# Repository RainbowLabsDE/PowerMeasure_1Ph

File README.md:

# PowerMeasure_1Ph

this repo is still undergoing major changes and should not yet be rebuilt

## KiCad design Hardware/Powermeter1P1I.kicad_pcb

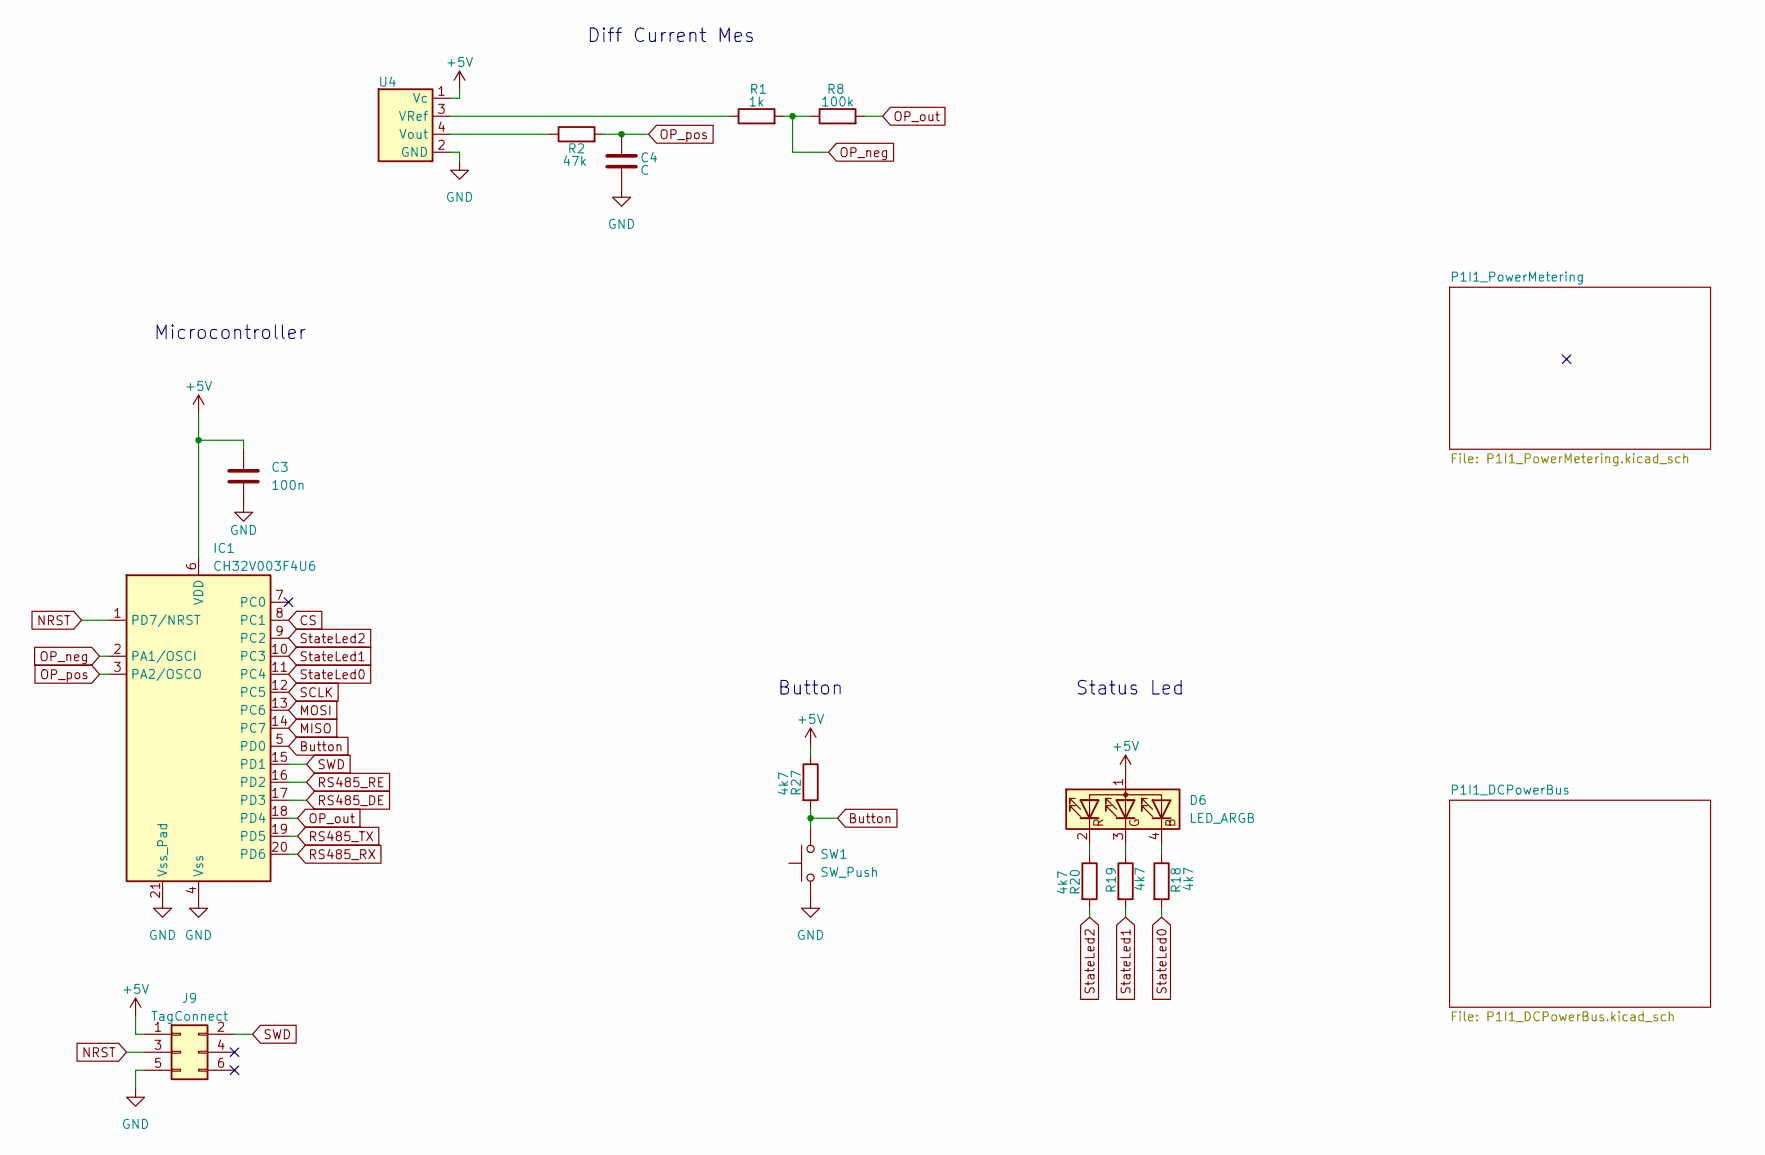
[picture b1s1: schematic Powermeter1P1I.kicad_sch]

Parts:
C3: 100n; C_0402_1005Metric
C4: C; C_0402_1005Metric
D6: LED_ARGB; LED-ARRAY-SMD_MHS110FRGBCT
IC1: CH32V003F4U6; QFN-20-1EP_3x3mm_P0.4mm_EP1.65x1.65mm_ThermalVias
J9: TagConnect; Tag-Connect_TC2030-IDC-NL_2x03_P1.27mm_Vertical
R1: 1k; R_0402_1005Metric
R2: 47k; R_0402_1005Metric
R8: 100k; R_0402_1005Metric
R18, R19, R20, R27: 4k7; R_0402_1005Metric
SW1: SW_Push; SW-SMD_TS24CA
U4: VACDiff

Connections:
+5V: C3.1, D6.1 (A), IC1.6 (VDD), J9.1, R27.1, U4.1 (Vc); also elsewhere on the board
Button: IC1.5 (PD0), R27.2, SW1.2
CS: IC1.8 (PC1); also elsewhere on the board
GND: C3.2, C4.2, IC1.4 (Vss), IC1.21 (Vss_Pad), J9.5, SW1.1, U4.2 (GND); also elsewhere on the board
MISO: IC1.14 (PC7); also elsewhere on the board
MOSI: IC1.13 (PC6); also elsewhere on the board
NRST: IC1.1 (PD7/NRST), J9.3
unnamed: D6.4 (BK), R18.1
unnamed: D6.3 (GK), R19.1
unnamed: D6.2 (RK), R20.1
unnamed: R1.1, U4.3 (VRef)
unnamed: R2.1, U4.4 (Vout)
OP_neg: IC1.2 (PA1/OSCI), R1.2, R8.1
OP_out: IC1.18 (PD4), R8.2
OP_pos: C4.1, IC1.3 (PA2/OSCO), R2.2
RS485_DE: IC1.17 (PD3); also elsewhere on the board
RS485_RE: IC1.16 (PD2); also elsewhere on the board
RS485_RX: IC1.20 (PD6); also elsewhere on the board
RS485_TX: IC1.19 (PD5); also elsewhere on the board
SCLK: IC1.12 (PC5); also elsewhere on the board
SWD: IC1.15 (PD1), J9.2
StateLed0: IC1.11 (PC4), R18.2
StateLed1: IC1.10 (PC3), R19.2
StateLed2: IC1.9 (PC2), R20.2

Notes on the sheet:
Status Led
Microcontroller
Button
Diff Current Mes

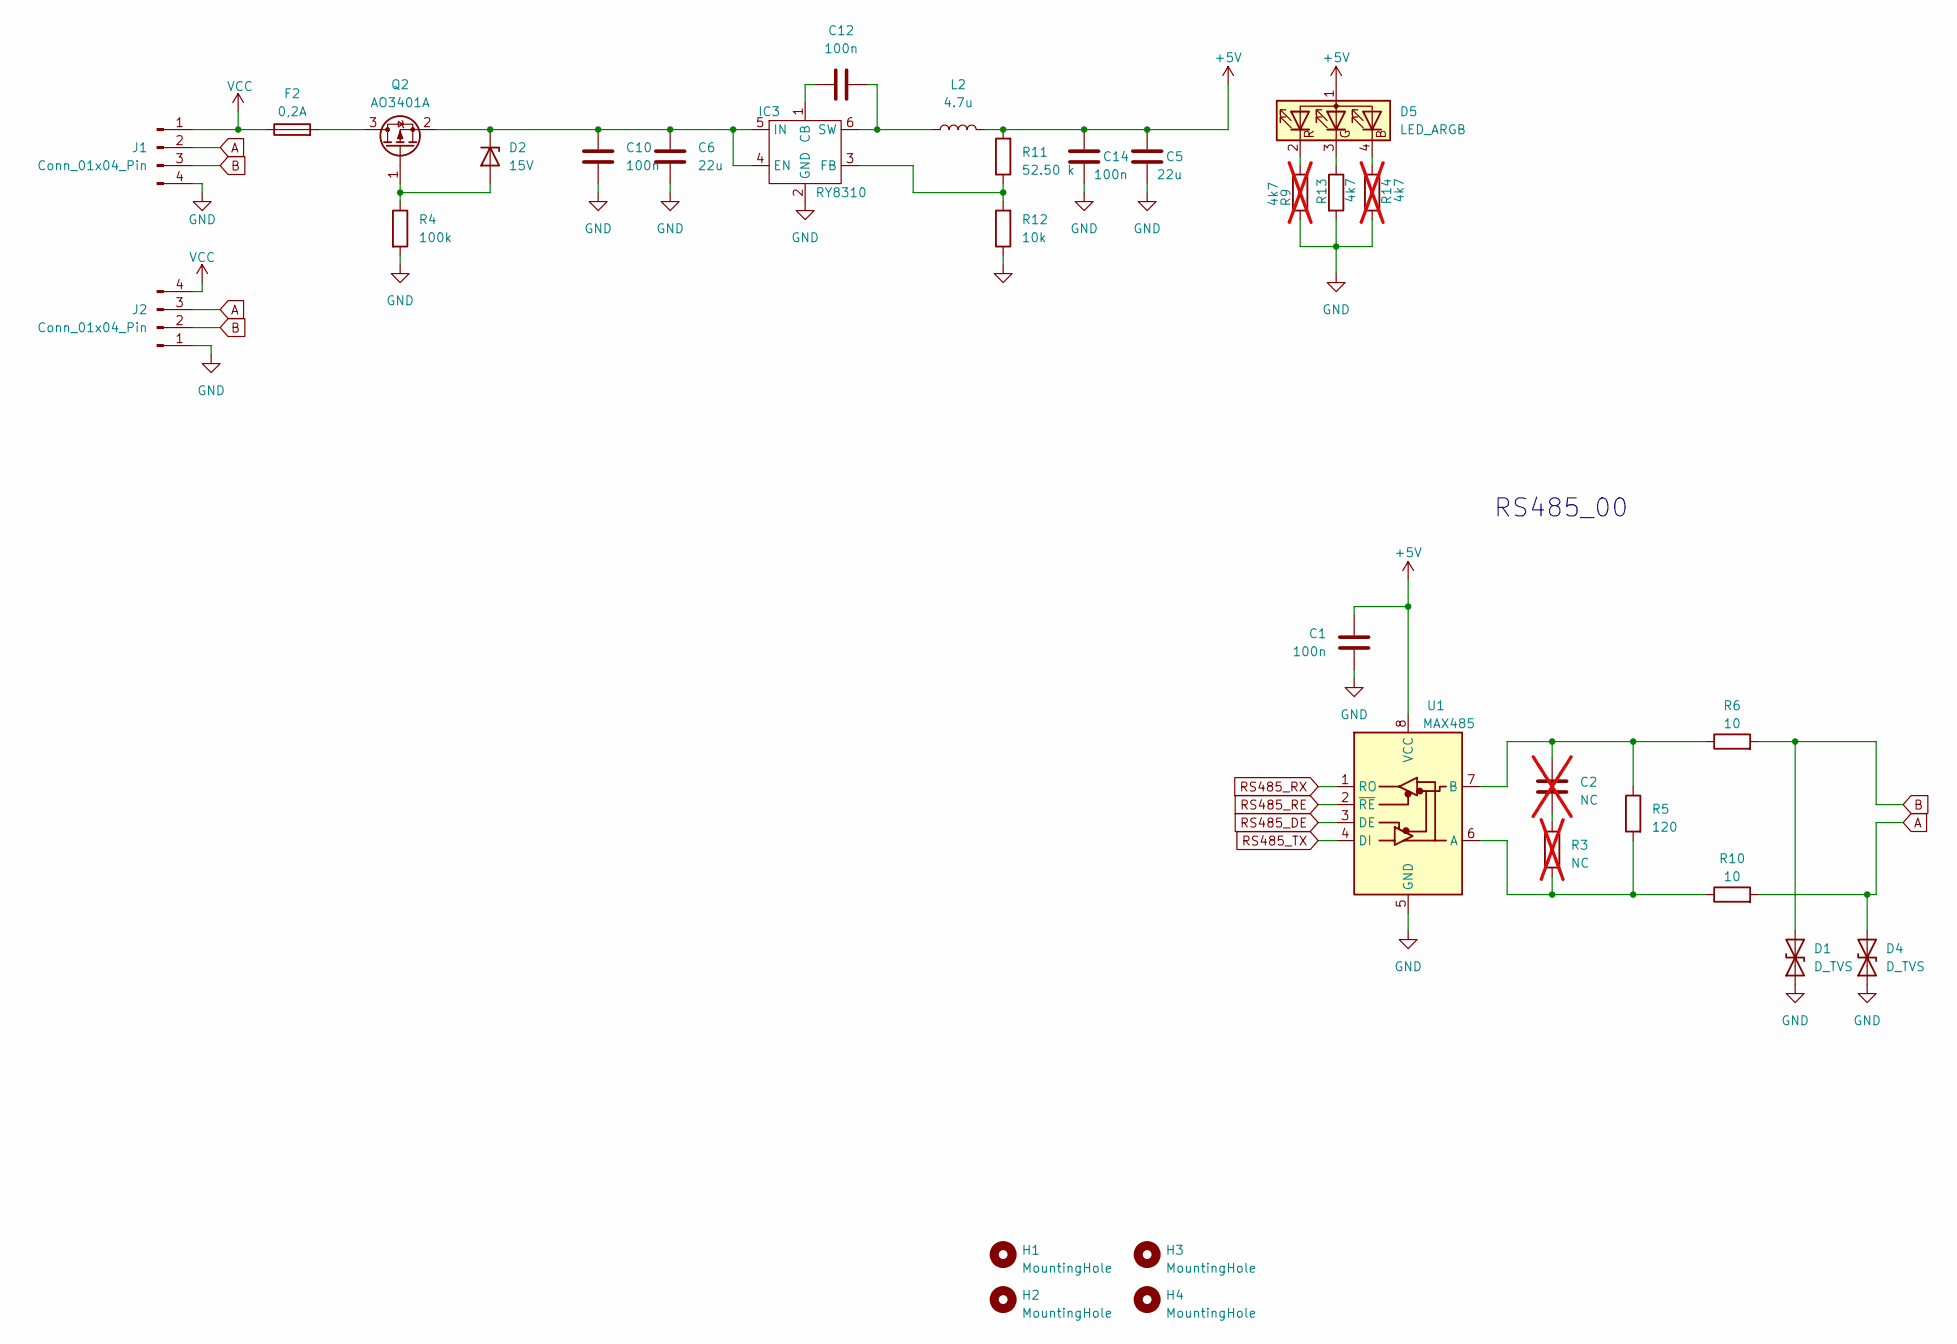
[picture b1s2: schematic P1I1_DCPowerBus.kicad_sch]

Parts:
C1, C10, C12, C14: 100n; C_0402_1005Metric
C2: NC; C_0402_1005Metric; not fitted
C5, C6: 22u; C_1210_3225Metric
D1, D4: D_TVS; D_0402_1005Metric
D2: 15V; D_SOD-323
D5: LED_ARGB; LED-ARRAY-SMD_MHS110FRGBCT
F2: 0,2A; Fuse_0603_1608Metric
H1, H2, H3, H4: MountingHole; MountingHole_4.3mm_M4
IC3: RY8310; SOT-23-6
J1, J2: Conn_01x04_Pin; CONN-SMD_HCZZ0451-4
L2: 4.7u; IND-SMD_L2.0-W1.6
Q2: AO3401A; TSOT-23
R3: NC; R_0402_1005Metric; not fitted
R4: 100k; R_0402_1005Metric
R5: 120; C_0402_1005Metric
R6, R10: 10; R_1206_3216Metric
R9, R14: 4k7; R_0402_1005Metric; not fitted
R11: 52.50 k; R_0402_1005Metric
R12: 10k; R_0402_1005Metric
R13: 4k7; R_0402_1005Metric
U1: MAX485; SOIC-8_3.9x4.9mm_P1.27mm

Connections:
+5V: C1.1, C5.1, C14.1, D5.1 (A), L2.2, R11.2, U1.8 (VCC); also elsewhere on the board
A: D4.2 (A2), J1.2, J2.3, R10.2
B: D1.2 (A2), J1.3, J2.2, R6.2
GND: C1.2, C5.2, C6.2, C10.2, C14.2, D1.1 (A1), D4.1 (A1), IC3.2 (GND), J1.4, J2.1, R4.2, R9.2, R12.1, R13.2, R14.2, U1.5 (GND); also elsewhere on the board
unnamed: C2.2, R3.2
unnamed: D2.2 (A), Q2.1 (G), R4.1
unnamed: C6.1, C10.1, D2.1 (K), IC3.4 (EN), IC3.5 (IN), Q2.2 (S)
unnamed: D5.4 (BK), R14.1
unnamed: D5.3 (GK), R13.1
unnamed: D5.2 (RK), R9.1
unnamed: C12.1, IC3.1 (CB)
unnamed: IC3.3 (FB), R11.1, R12.2
unnamed: C12.2, IC3.6 (SW), L2.1
unnamed: F2.2, Q2.3 (D)
unnamed: R3.1, R5.2, R10.1, U1.6 (A)
unnamed: C2.1, R5.1, R6.1, U1.7 (B)
RS485_DE: U1.3 (DE); also elsewhere on the board
RS485_RE: U1.2 (~RE); also elsewhere on the board
RS485_RX: U1.1 (RO); also elsewhere on the board
RS485_TX: U1.4 (DI); also elsewhere on the board
VCC: F2.1, J1.1, J2.4

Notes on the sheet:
RS485_00

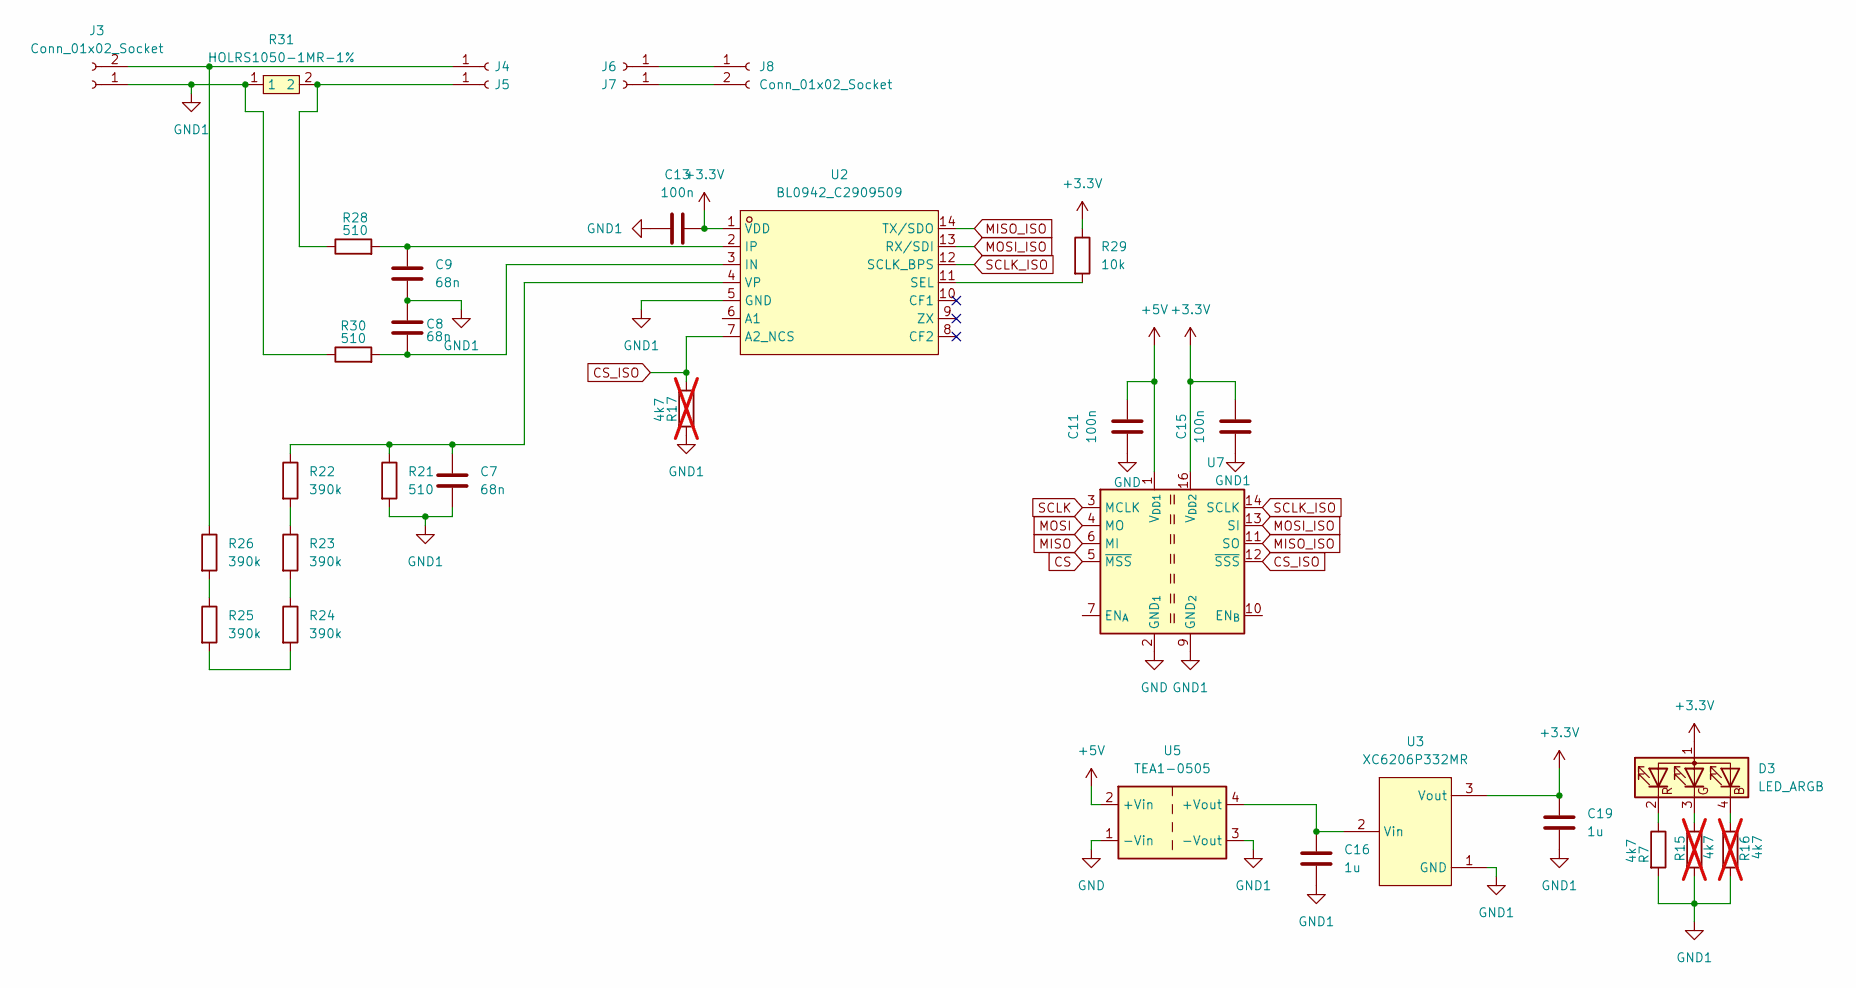
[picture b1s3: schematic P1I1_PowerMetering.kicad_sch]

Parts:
C7, C8, C9: 68n; C_0402_1005Metric
C11, C13, C15: 100n; C_0402_1005Metric
C16, C19: 1u; C_0402_1005Metric
D3: LED_ARGB; LED-ARRAY-SMD_MHS110FRGBCT
J3, J8: Conn_01x02_Socket; LPT2,5-2-5,0
J4, J5, J6, J7: Conn_01x01_Socket; TestPoint_THTPad_3.0x3.0mm_Drill1.5mm
R7: 4k7; R_0402_1005Metric
R15, R16, R17: 4k7; R_0402_1005Metric; not fitted
R21, R28, R30: 510; R_0603_1608Metric
R22, R23, R24, R25, R26: 390k; R_0603_1608Metric
R29: 10k; R_0402_1005Metric
R31: HOLRS1050-1MR-1%; R3920; LCSC Part C481472
U2: BL0942_C2909509; TSSOP-14_L5.0-W4.4-P0.65-LS6.4-BL; LCSC Part C2909509
U3: XC6206P332MR; SOT-23-3_L2.9-W1.6-P1.90-LS2.8-BR; LCSC Part C5446
U5: TEA1-0505; Converter_DCDC_TRACO_TEA1-xxxx_THT
U7: SOIC-16W_7.5x10.3mm_P1.27mm

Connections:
+3.3V: C13.2, C15.2, C19.1, D3.1 (A), R29.1, U2.1 (VDD), U3.3 (Vout), U7.16 (V_{DD2})
+5V: C11.2, U5.2 (+Vin), U7.1 (V_{DD1}); also elsewhere on the board
CS: U7.5 (~MSS); also elsewhere on the board
CS_ISO: R17.1, U2.7 (A2_NCS), U7.12 (~SSS)
GND: C11.1, U5.1 (-Vin), U7.2 (GND_{1}), U7.8 (GND_{1}); also elsewhere on the board
GND1: C7.2, C8.1, C9.2, C13.1, C15.1, C16.2, C19.2, J3.1, R7.2, R15.2, R16.2, R17.2, R21.2, R30.1, R31.1, U2.5 (GND), U3.1 (GND), U5.3 (-Vout), U7.9 (GND_{2}), U7.15 (GND_{2})
MISO: U7.6 (MI); also elsewhere on the board
MISO_ISO: U2.14 (TX/SDO), U7.11 (SO)
MOSI: U7.4 (MO); also elsewhere on the board
MOSI_ISO: U2.13 (RX/SDI), U7.13 (SI)
unnamed: D3.4 (BK), R16.1
unnamed: D3.3 (GK), R15.1
unnamed: D3.2 (RK), R7.1
unnamed: J3.2, J4.1, R26.1
unnamed: J5.1, R28.1, R31.2
unnamed: J6.1, J8.1
unnamed: J7.1, J8.2
unnamed: R22.2, R23.1
unnamed: R23.2, R24.1
unnamed: R24.2, R25.2
unnamed: R25.1, R26.2
unnamed: C8.2, R30.2, U2.3 (IN)
unnamed: C9.1, R28.2, U2.2 (IP)
unnamed: R29.2, U2.11 (SEL)
unnamed: C7.1, R21.1, R22.1, U2.4 (VP)
unnamed: C16.1, U3.2 (Vin), U5.4 (+Vout)
SCLK: U7.3 (MCLK); also elsewhere on the board
SCLK_ISO: U2.12 (SCLK_BPS), U7.14 (SCLK)

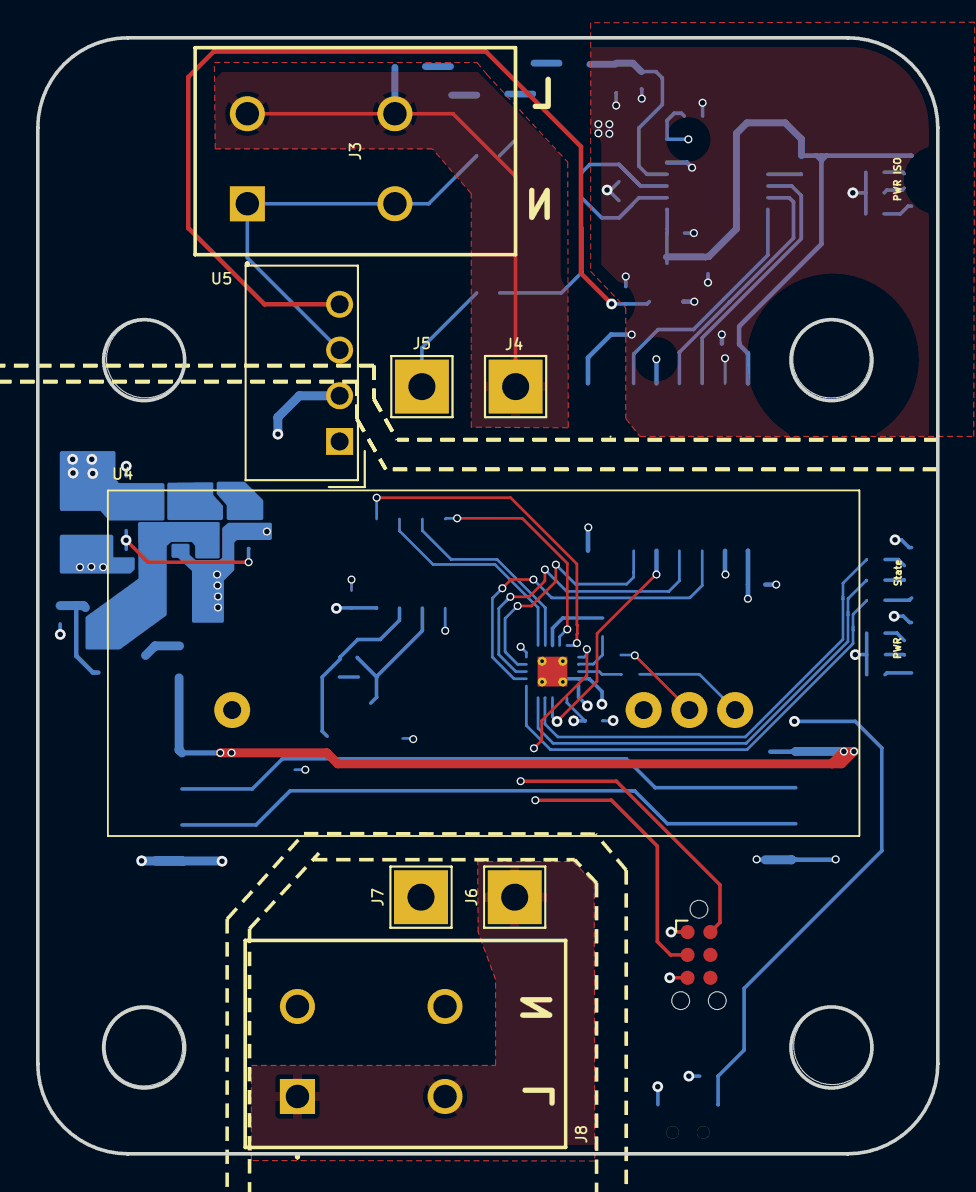
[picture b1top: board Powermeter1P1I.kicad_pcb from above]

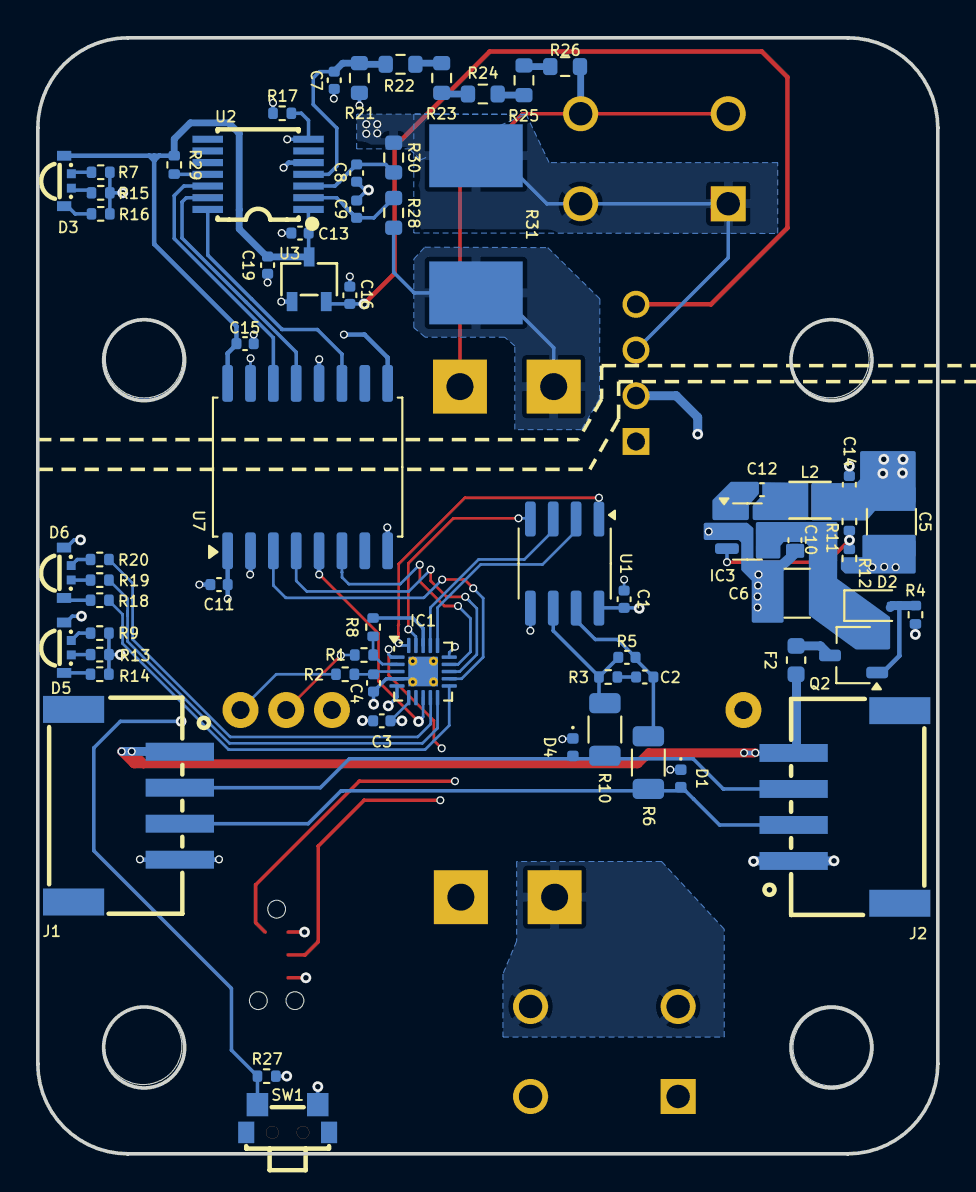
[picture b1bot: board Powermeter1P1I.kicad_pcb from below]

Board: 4 copper layers, 50.0 x 62.0 mm, 79 parts (66 on the bottom side), 61 nets.

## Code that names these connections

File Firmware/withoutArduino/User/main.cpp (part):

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

/********* Modbus *********/
// TX - PD5
// RX - PD6
// DE - PD3
// RE - PD2 (active low)
/********* Led und Button **********/
// State LED R - PC4
// State LED G - PC3
// State LED B - PC2
// Button - PD0
/********* Stommessung *********/
// OP_neg - PA1
// OP_pos - PA2
// OP_out - PD4
/********* Powermonitoring *********/
// SCLK - PC5
// MOSI - PC6
// MISO - PC7
// CS - PC1

#define PIN_LEDR GPIOC, GPIO_Pin_4
#define PIN_LEDG GPIOC, GPIO_Pin_3
#define PIN_LEDB GPIOC, GPIO_Pin_2
#define PIN_RS485_DE GPIOD, GPIO_Pin_3
#define PIN_RS485_RE GPIOD, GPIO_Pin_2

#define NO_DATA_TIMEOUT 2000

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//  */
// void TIM1_PWMOut_Init(u16 arr, u16 psc, u16 ccp) {
//     RCC_APB2PeriphClockCmd(RCC_APB2Periph_AFIO, ENABLE);
//     GPIO_PinRemapConfig(GPIO_PartialRemap1_TIM1, ENABLE); // CH1-4: PC6, PC7, PC0, PD3

//     GPIO_InitTypeDef GPIO_InitStructure = {0};
//     TIM_OCInitTypeDef TIM_OCInitStructure = {0};
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    GPIO_WriteBit(PIN_LEDR, Bit_SET);       // turn off LED
    GPIO_WriteBit(PIN_LEDG, Bit_SET);       // turn off LED
    GPIO_WriteBit(PIN_LEDB, Bit_SET);       // turn off LED
    GPIO_WriteBit(PIN_RS485_DE, Bit_RESET); // disable send
    GPIO_WriteBit(PIN_RS485_RE, Bit_RESET); // enable receive (active low)
}

// void updateDataWindow(RBLB* rblbInst) {
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
inline void rs485_de()
{
    GPIO_WriteBit(PIN_RS485_DE, Bit_SET);
    GPIO_WriteBit(PIN_RS485_RE, Bit_SET);
}
inline void rs485_re()
{
    GPIO_WriteBit(PIN_RS485_DE, Bit_RESET);
    GPIO_WriteBit(PIN_RS485_RE, Bit_RESET);
}

void rs485Write(const uint8_t *buf, size_t size)
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
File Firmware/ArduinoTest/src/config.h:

#include "Arduino.h"

const int StateLed0 = PC4;
const int StateLed1 = PC3;
const int StateLed2 = PC2;

const int ButtonPin = PD0;

const int RePin = PD2;
const int dePin = PD3;

const int OpOut = PD4;


#define MODBUS_SERIAL Serial
#define MODBUS_BAUD 38400
#define MODBUS_CONFIG SERIAL_8N1
static int MODBUS_UNIT_ID =  1;

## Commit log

2024-11-22 Update README.md
    add Warning
2024-11-22 add Files
2024-11-22 add Schematic PDF
2025-02-13 add all
2025-02-13 fix Silkscreen
2025-02-13 isolation slot and silkscreen tweaks
2025-05-16 add firmeware files
2025-05-22 add spi and BL0942
2025-05-22 fix SPI & BL0942 communication
2025-05-22 implement BL0942 read_STATUS
2025-05-23 fix delay() not working, when using SDI Print
2025-06-05 add workaround for SDI printf bug
